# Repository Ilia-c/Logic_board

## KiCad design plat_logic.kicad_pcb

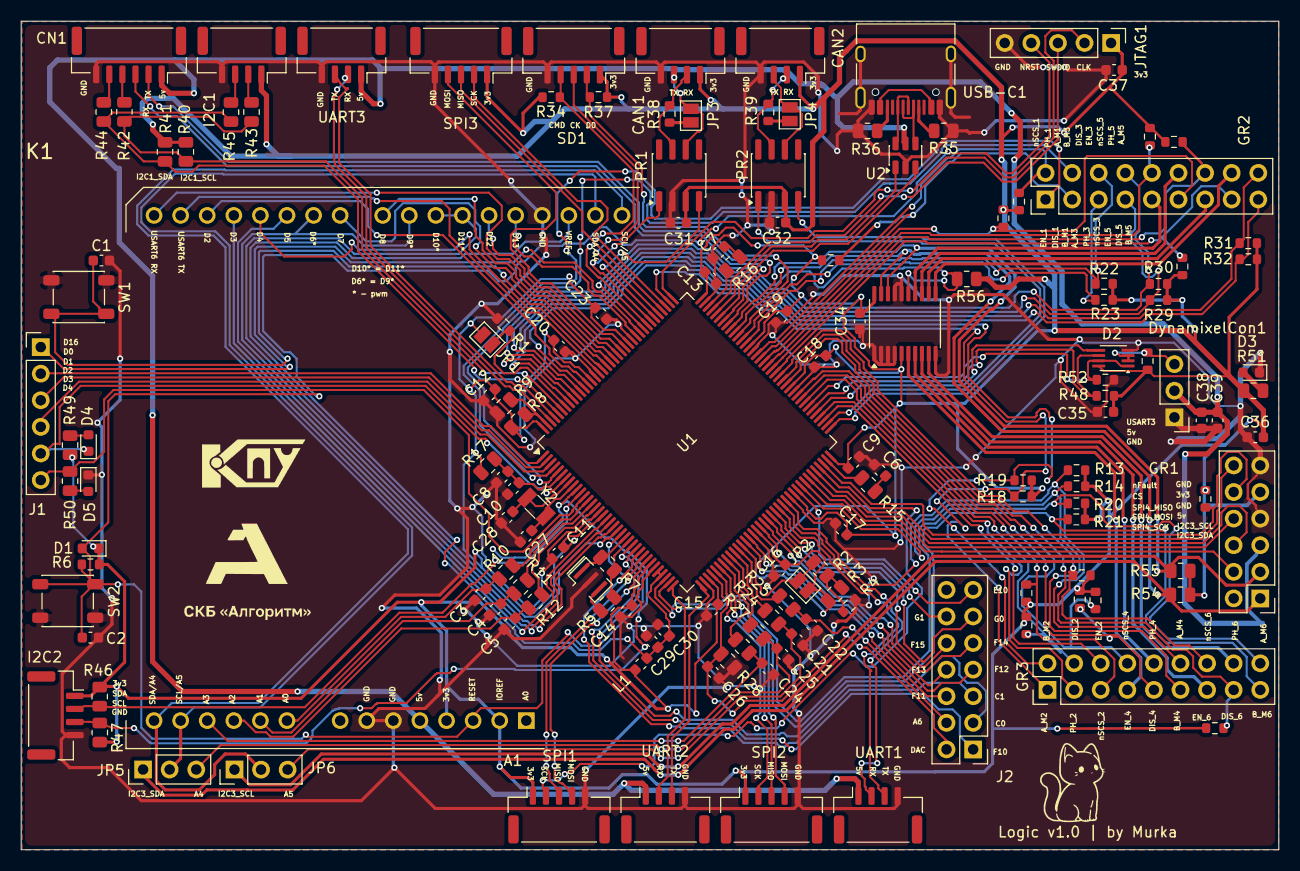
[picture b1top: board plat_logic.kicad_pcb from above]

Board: 2 copper layers, 120.1 x 79.1 mm, 149 parts (0 on the bottom side), 164 nets.

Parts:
A1: Arduino_UNO_R3
C1, C2, C3, C4, C5, C9, C10, C11, C12, C13, C14, C15, C16, C17, C18, C19, C20, C21, C22, C23, C24, C25, C29, C31, C32, C34, C35, C36, C38: 100nF; C_0603_1608Metric
C6, C7: 2.2uF; C_0603_1608Metric
C8: 1uF x5r; C_0603_1608Metric
C26: 22pF; C_0603_1608Metric
C27, C28: 10pF; C_0603_1608Metric
C30, C37: 1uF; C_0603_1608Metric
C39: 10uF; C_0603_1608Metric
CAN1, CAN2: SM04B-GHS-TB(LF)(SN); JST_GH_SM04B-GHS-TB_1x04-1MP_P1.25mm_Horizontal
CN1: GPS_Port; JST_GH_SM06B-GHS-TB_1x06-1MP_P1.25mm_Horizontal
D1: BAS70; D_0603_1608Metric
D2: SN74LVC2G241DCUR; VSSOP-8_2.3x2mm_P0.5mm
D3, D4, D5: led; LED_0603_1608Metric
DynamixelCon1: PinHeader_1x03_P2.54mm_Vertical
GR1: Conn_01x12_Pin; PinHeader_2x06_P2.54mm_Vertical
GR2, GR3: Conn_01x18_Pin; PinHeader_2x09_P2.54mm_Vertical
I2C1, I2C2: SM04B-GHS-TB(LF)(SN); JST_GH_SM04B-GHS-TB_1x04-1MP_P1.25mm_Horizontal
J1: Conn_01x06_Pin; PinHeader_1x06_P2.54mm_Vertical
J2: Conn_01x14_Pin; PinHeader_2x07_P2.54mm_Vertical
JP1, JP2, JP3, JP4: Jumper_2_Open; SolderJumper-2_P1.3mm_Open_Pad1.0x1.5mm
JP5, JP6: Jumper_3_Open; PinHeader_1x03_P2.54mm_Vertical
JTAG1: DS1023-1X5SF11; PinHeader_1x05_P2.54mm_Vertical
K1: Kontur; JetBot_logicKontur
L1: BLM18AG102SN1D (1kOm); L_0603_1608Metric
PR1, PR2: SN65HVD232; SOIC-8_3.9x4.9mm_P1.27mm
PWM_control1: PCA9634; TSSOP-20_4.4x6.5mm_P0.65mm
R1, R4, R6: 10K; R_0603_1608Metric
R2: 100K; R_0805_2012Metric
R3, R8, R9, R15, R16, R17: 0; R_0805_2012Metric
R5, R51: 330; R_0805_2012Metric
R7: 1M; R_0805_2012Metric
R10, R11, R12, R24, R25, R26, R27: 47; R_0805_2012Metric
R13, R14, R18, R19, R20, R21, R22, R23, R29, R30, R31, R32: 2.2k; R_0603_1608Metric
R28: 27K; R_0805_2012Metric
R34, R37, R48, R52, R53, R58, R59, R60, R61, R62, R63, R64, R65, R66, R67, R68, R69, R70: 10k; R_0603_1608Metric
R35, R36: 5.1k; R_0805_2012Metric
R38, R39: 120; R_0603_1608Metric
R40, R41, R46, R47, R54, R55, R56: 1K5; R_0805_2012Metric
R42, R43, R44, R45: 22; R_0805_2012Metric
R49: 1k; R_0805_2012Metric
R50: 100; R_0805_2012Metric
SD1: SM05B-GHS-TB; JST_GH_SM05B-GHS-TB_1x05-1MP_P1.25mm_Horizontal
SPI1, SPI2, SPI3: SM05B-GHS-TB; JST_GH_SM05B-GHS-TB_1x05-1MP_P1.25mm_Horizontal
SW1, SW2: Button-SMD-4.5x4.5x5.5; SW_SPST_PTS647_Sx50
U1: STM32F429ZITx; LQFP-144_20x20mm_P0.5mm
U2: USBLC6-2SC6; SOT-23-6
UART1, UART2, UART3: SM04B-GHS-TB(LF)(SN); JST_GH_SM04B-GHS-TB_1x04-1MP_P1.25mm_Horizontal
USB-C1: USB_C_Receptacle; USB_C_Receptacle_HRO_TYPE-C-31-M-12
Y1: CSTNE8M00GH5L000R0 8.000MHZ; Resonator_SMD_Murata_CSTxExxV-3Pin_3.0x1.1mm
Y2: NX3215SA-32.768KHZ-EXS00A-MU00746; Crystal_SMD_3215-2Pin_3.2x1.5mm

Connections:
+3v3: A1.2 (IOREF), A1.4 (3V3), C9.1, C11.2, C12.1, C13.2, C14.2, C15.2, C16.2, C17.2, C18.2, C19.2, C20.2, C23.2, C31.1, C32.1, C34.2, C35.1, C36.1, C37.1, CAN1.1, CAN2.1, D1.1 (K), D2.8 (VCC), GR1.9, I2C1.1, I2C2.1, JP1.2 (B), JP2.1 (A), JTAG1.1, L1.1, PR1.3 (VCC), PR2.3 (VCC), PWM_control1.5 (A4), PWM_control1.20 (VDD), R3.1, R6.2, R8.1, R13.1, R14.2, R17.1, R18.1, R19.1, R20.2, R21.2, R22.2, R23.1, R29.1, R30.1, R31.2, R32.2, R34.1, R37.1, R40.1, R41.1, R46.1, R47.1, R48.1, R49.1, R51.1, R53.1, R54.1, R55.1, R56.1, R58.1, R59.1, R60.1, R61.1, R62.1, R63.1, R64.1, R65.1, R66.1, R67.1, R68.1, R69.1, R70.1, SD1.1, SPI1.1, SPI2.1, SPI3.1, U1.17 (VDD), U1.30 (VDD), U1.39 (VDD), U1.52 (VDD), U1.62 (VDD), U1.72 (VDD), U1.84 (VDD), U1.95 (VDD), U1.108 (VDD), U1.121 (VDD), U1.131 (VDD), U1.144 (VDD)
+5v: A1.5 (+5V), C38.1, C39.1, CN1.1, DynamixelCon1.2 (VDD), GR1.5, U2.5 (VBUS), UART1.1, UART2.1, UART3.1
/Connectivity_Peripheral/CAN1_H: CAN1.2, PR1.7 (CANH), R38.1
/Connectivity_Peripheral/CAN1_L: CAN1.3, JP3.2 (B), PR1.6 (CANL)
/Connectivity_Peripheral/CAN2_H: CAN2.2, PR2.7 (CANH), R39.1
/Connectivity_Peripheral/CAN2_L: CAN2.3, JP4.2 (B), PR2.6 (CANL)
/Connectivity_Peripheral/DXL_DATA: D2.2 (1A), D2.3 (2Y), DynamixelCon1.3 (Data), R53.2
/Connectivity_Peripheral/VBUS: USB-C1.A4 (VBUS), USB-C1.A9 (VBUS), USB-C1.B4 (VBUS), USB-C1.B9 (VBUS)
/MCU/VBAT: C8.2, C10.2, R17.2, U1.6 (VBAT)
A0: A1.9 (A0), C3.2, R10.1
A1: A1.10 (A1), C4.1, R11.1
A2: A1.11 (A2), C5.1, R12.1
A3: A1.12 (A3), C24.2, R26.1
A4: C25.1, JP5.3 (B), R27.1
A5: C21.2, JP6.3 (B), R24.1
A6: C22.1, J2.4, R25.1
BOOT0: JP1.1 (A), R1.1, U1.138 (BOOT0)
BOOT1: JP2.2 (B), R2.2, U1.48 (PB2)
CAN1_RX: PR1.4 (R), U1.114 (PD0)
CAN1_TX: PR1.1 (D), U1.115 (PD1)
CAN2_RX: PR2.4 (R), U1.73 (PB12)
CAN2_TX: PR2.1 (D), U1.74 (PB13)
CLK: JTAG1.2, U1.109 (PA14)
CS: GR1.10, R70.2, U1.70 (PB11)
D0: J1.2, U1.1 (PE2)
D1: J1.3, U1.2 (PE3)
D2: J1.4, U1.3 (PE4)
D2_ard: A1.17 (D2), U1.132 (PG15)
D3: D4.1 (K), J1.5, U1.7 (PC13)
D3_ard: A1.18 (D3), U1.18 (PF6)
D4: J1.6, R50.1, U1.12 (PF2)
D4_ard: A1.19 (D4), U1.128 (PG13)
D5: J2.1, U1.22 (PF10)
D5_ard: A1.20 (D5), U1.19 (PF7)
D6: J2.3, U1.26 (PC0)
D6_D9_ard: A1.21 (D6), A1.24 (D9), U1.20 (PF8)
D7: J2.5, U1.27 (PC1)
D7_ard: A1.22 (D7), U1.126 (PG11)
D8: J2.6, U1.49 (PF11)
D8_ard: A1.23 (D8), U1.125 (PG10)
D9: J2.7, U1.50 (PF12)
D10: J2.8, U1.53 (PF13)
D10_D11_ard: A1.25 (D10), A1.26 (D11), U1.21 (PF9)
D11: J2.9, U1.54 (PF14)
D12: J2.10, U1.55 (PF15)
D12_ard: A1.27 (D12), U1.123 (PD7)
D13: J2.11, U1.56 (PG0)
D13_ard: A1.28 (D13), U1.119 (PD5)
D14: J2.12, U1.57 (PG1)
D15: J2.13, U1.63 (PE10)
D16: J1.1, U1.118 (PD4)
DAC: C26.1, J2.2, R28.1, U1.40 (PA4)
DISABLE_1: GR2.3, R58.2, U1.92 (PG7)
DISABLE_2: GR3.4, R59.2, U1.80 (PD11)
DISABLE_3: GR2.10, R60.2, U1.90 (PG5)
DISABLE_4: GR3.9, R61.2, U1.82 (PD13)
DISABLE_5: GR2.15, R62.2, U1.88 (PG3)
DISABLE_6: GR3.15, R63.2, U1.86 (PD15)
ENC_A_M1_mk: GR2.6, R22.1, U1.96 (PC6)
ENC_A_M2_mk: GR3.1, R18.2, U1.110 (PA15)
ENC_A_M3_mk: GR2.7, R29.2, U1.134 (PB4)
ENC_A_M4_mk: GR3.12, R13.2, U1.60 (PE9)
ENC_A_M5_mk: GR2.18, R31.1, U1.136 (PB6)
ENC_A_M6_mk: GR3.18, R20.1, U1.34 (PA0)
ENC_B_M1_mk: GR2.5, R23.2, U1.97 (PC7)
ENC_B_M2_mk: GR3.2, R19.2, U1.133 (PB3)
ENC_B_M3_mk: GR2.8, R30.2, U1.135 (PB5)
ENC_B_M4_mk: GR3.11, R14.1, U1.64 (PE11)
ENC_B_M5_mk: GR2.17, R32.1, U1.137 (PB7)
ENC_B_M6_mk: GR3.17, R21.1, U1.35 (PA1)
EN_1: GR2.1, U1.4 (PE5)
EN_2: GR3.6, U1.75 (PB14)
EN_3: GR2.12, PWM_control1.13 (LED6)
EN_4: GR3.7, PWM_control1.6 (LED0)
EN_5: GR2.13, PWM_control1.12 (LED5)
EN_6: GR3.13, PWM_control1.8 (LED2)
GND: A1.6 (GND), A1.7 (GND), A1.29 (GND), C1.2, C2.2, C3.1, C4.2, C5.2, C6.1, C7.1, C8.1, C9.2, C10.1, C11.1, C12.2, C13.1, C14.1, C15.1, C16.1, C17.1, C18.1, C19.1, C20.1, C21.1, C22.2, C23.1, C24.1, C25.2, C26.2, C27.2, C28.2, C29.2, C30.1, C31.2, C32.2, C34.1, C35.2, C36.2, C37.2, C38.2, C39.2, CAN1.4, CAN2.4, CN1.6, D2.4 (GND), D3.1 (K), D5.1 (K), DynamixelCon1.1 (GND), GR1.7, GR1.11, I2C1.4, I2C2.4, JTAG1.5, PR1.2 (GND), PR2.2 (GND), PWM_control1.1 (A0), PWM_control1.2 (A1), PWM_control1.3 (A2), PWM_control1.4 (A3), PWM_control1.10 (VSS), PWM_control1.16 (A5), PWM_control1.17 (A6), R1.2, R4.1, R9.2, R28.2, R35.1, R36.1, R52.2, SD1.5, SPI1.5, SPI2.5, SPI3.5, SW1.2, SW2.2, U1.16 (VSS), U1.31 (VSSA), U1.38 (VSS), U1.51 (VSS), U1.61 (VSS), U1.83 (VSS), U1.94 (VSS), U1.107 (VSS), U1.120 (VSS), U1.130 (VSS), U2.2 (GND), UART1.4, UART2.4, UART3.4, USB-C1.A1 (GND), USB-C1.A12 (GND), USB-C1.B1 (GND), USB-C1.B12 (GND), USB-C1.SH (SHIELD), Y1.2
I2C1_SCL: R40.2, R42.2, R43.2, U1.139 (PB8)
I2C1_SDA: R41.2, R44.2, R45.2, U1.140 (PB9)
I2C2_SCL: I2C2.2, R46.2, U1.11 (PF1)
I2C2_SDA: I2C2.3, R47.2, U1.10 (PF0)
I2C3_SCL: GR1.3, JP6.1 (A), PWM_control1.18 (SCL), R55.2, U1.100 (PA8)
I2C3_SDA: GR1.1, JP5.1 (A), PWM_control1.19 (SDA), R54.2, U1.99 (PC9)
NRST: A1.3 (~RESET), C2.1, D1.2 (A), JTAG1.4, R6.1, SW2.1, U1.25 (NRST)
unnamed: C6.2, R15.1
unnamed: C7.2, R16.1
unnamed: CN1.4, R42.1
unnamed: CN1.5, R44.1
unnamed: D3.2 (A), R51.2
unnamed: D4.2 (A), R49.2
unnamed: D5.2 (A), R50.2
unnamed: I2C1.2, R43.1
unnamed: I2C1.3, R45.1
unnamed: JP3.1 (A), R38.2
unnamed: JP4.1 (A), R39.2
unnamed: A1.13 (SDA/A4), A1.31 (SDA/A4), JP5.2 (C)
unnamed: A1.14 (SCL/A5), A1.32 (SCL/A5), JP6.2 (C)
unnamed: R2.1, R3.2, R4.2
unnamed: R5.2, Y1.3
unnamed: U1.103 (PA11), U2.3 (I/O2)
unnamed: U1.104 (PA12), U2.1 (I/O1)
unnamed: R24.2, U1.46 (PB0)
unnamed: R25.2, U1.47 (PB1)
unnamed: R26.2, U1.44 (PC4)
unnamed: R27.2, U1.45 (PC5)
unnamed: R8.2, R9.1, U1.143 (PDR_ON)
unnamed: R10.2, U1.13 (PF3)
unnamed: R11.2, U1.14 (PF4)
unnamed: R12.2, U1.15 (PF5)
unnamed: C1.1, SW1.1, U1.127 (PG12)
unnamed: R15.2, U1.71 (VCAP_1)
unnamed: R16.2, U1.106 (VCAP_2)
unnamed: R35.2, USB-C1.A5 (CC1)
unnamed: R36.2, USB-C1.B5 (CC2)
OE*: PWM_control1.15 (OE#), R56.2, U1.117 (PD3)
PC14: C28.1, U1.8 (PC14), Y2.1
PC15: C27.1, U1.9 (PC15), Y2.2
PH0: R7.1, U1.23 (PH0), Y1.1
PH1: R5.1, R7.2, U1.24 (PH1)
PH_1: GR2.4, U1.5 (PE6)
PH_2: GR3.3, U1.76 (PB15)
PH_3: GR2.9, PWM_control1.14 (LED7)
PH_4: GR3.10, PWM_control1.7 (LED1)
PH_5: GR2.16, PWM_control1.11 (LED4)
PH_6: GR3.16, PWM_control1.9 (LED3)
SDIO_CK: SD1.3, U1.113 (PC12)
SDIO_CMD: R34.2, SD1.4, U1.116 (PD2)
SDIO_D0: R37.2, SD1.2, U1.98 (PC8)
SPI1_MISO: SPI2.3, U1.42 (PA6)
SPI1_MOSI: SPI2.4, U1.43 (PA7)
SPI1_SCK: SPI2.2, U1.41 (PA5)
SPI2_MISO: SPI1.3, U1.28 (PC2)
SPI2_MOSI: SPI1.4, U1.29 (PC3)
SPI2_SCK: SPI1.2, U1.69 (PB10)
SPI3_MISO: SPI3.3, U1.112 (PC11)
SPI3_MOSI: SPI3.4, U1.122 (PD6)
SPI3_SCK: SPI3.2, U1.111 (PC10)
SPI4_MISO: GR1.8, U1.66 (PE13)
SPI4_MOSI: GR1.6, U1.67 (PE14)
SPI4_SCK: GR1.4, U1.65 (PE12)
SWDIO: JTAG1.3, U1.105 (PA13)
UART7_RX: U1.58 (PE7), UART1.3
UART7_TX: U1.59 (PE8), UART1.2
UART8_RX: U1.141 (PE0), UART3.3
UART8_TX: U1.142 (PE1), UART3.2
USART1_RX: CN1.3, U1.102 (PA10)
USART1_TX: CN1.2, U1.101 (PA9)
USART2_RX: U1.37 (PA3), UART2.3
USART2_TX: U1.36 (PA2), UART2.2
USART3_RX: D2.6 (1Y), R48.2, U1.78 (PD9)
USART3_TX: D2.5 (2A), U1.77 (PD8)
USART3_TX_EN: D2.1 (1OE#), D2.7 (2OE), R52.1, U1.79 (PD10)
USART6_RX_D0: A1.15 (D0/RX), U1.124 (PG9)
USART6_TX_D1: A1.16 (D1/TX), U1.129 (PG14)
USB_DM: U2.4 (I/O2), USB-C1.A7 (D-), USB-C1.B7 (D-)
USB_DP: U2.6 (I/O1), USB-C1.A6 (D+), USB-C1.B6 (D+)
VDDA: A1.30 (AREF), C29.1, C30.2, L1.2, U1.32 (VREF+), U1.33 (VDDA)
nFault: GR1.12, U1.68 (PE15)
nSCS_1: GR2.2, R64.2, U1.93 (PG8)
nSCS_2: GR3.5, R65.2, U1.81 (PD12)
nSCS_3: GR2.11, R66.2, U1.91 (PG6)
nSCS_4: GR3.8, R67.2, U1.85 (PD14)
nSCS_5: GR2.14, R68.2, U1.89 (PG4)
nSCS_6: GR3.14, R69.2, U1.87 (PG2)
